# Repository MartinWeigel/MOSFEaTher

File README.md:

# MOSFEaTher

This PCB provides control of eight MOSFET outputs. These can be controlled through an [Adafruit Feather HUZZAH32](https://www.adafruit.com/product/3405) microcontroller. It is a two-layer PCB and all parts can be handsoldered in case that costs are a concern.

This board was designed using [KiCad 6.0](http://www.kicad.org).

## Design

## Parts
The board requires the following parts. All of them should be easy to handsolder:

Part                   | Quantity | Description
-----------------------|----------|----------------------------
Feather HUZZAH32       | 1        | ESP32 Microcontroller
Phoenix MPT-0,5-2-2.54 | 8        | 2-pin Terminalblock
IRLR024N DPAK MOSFET   | 8        | N-Channel MOSFET (55V 17A)
0805 Resistor 470 Ohm  | 8        | Generic Resistor

## License
<br />This work is licensed under a <a rel="license" href="http://creativecommons.org/licenses/by/4.0/">Creative Commons Attribution 4.0 International License</a>.

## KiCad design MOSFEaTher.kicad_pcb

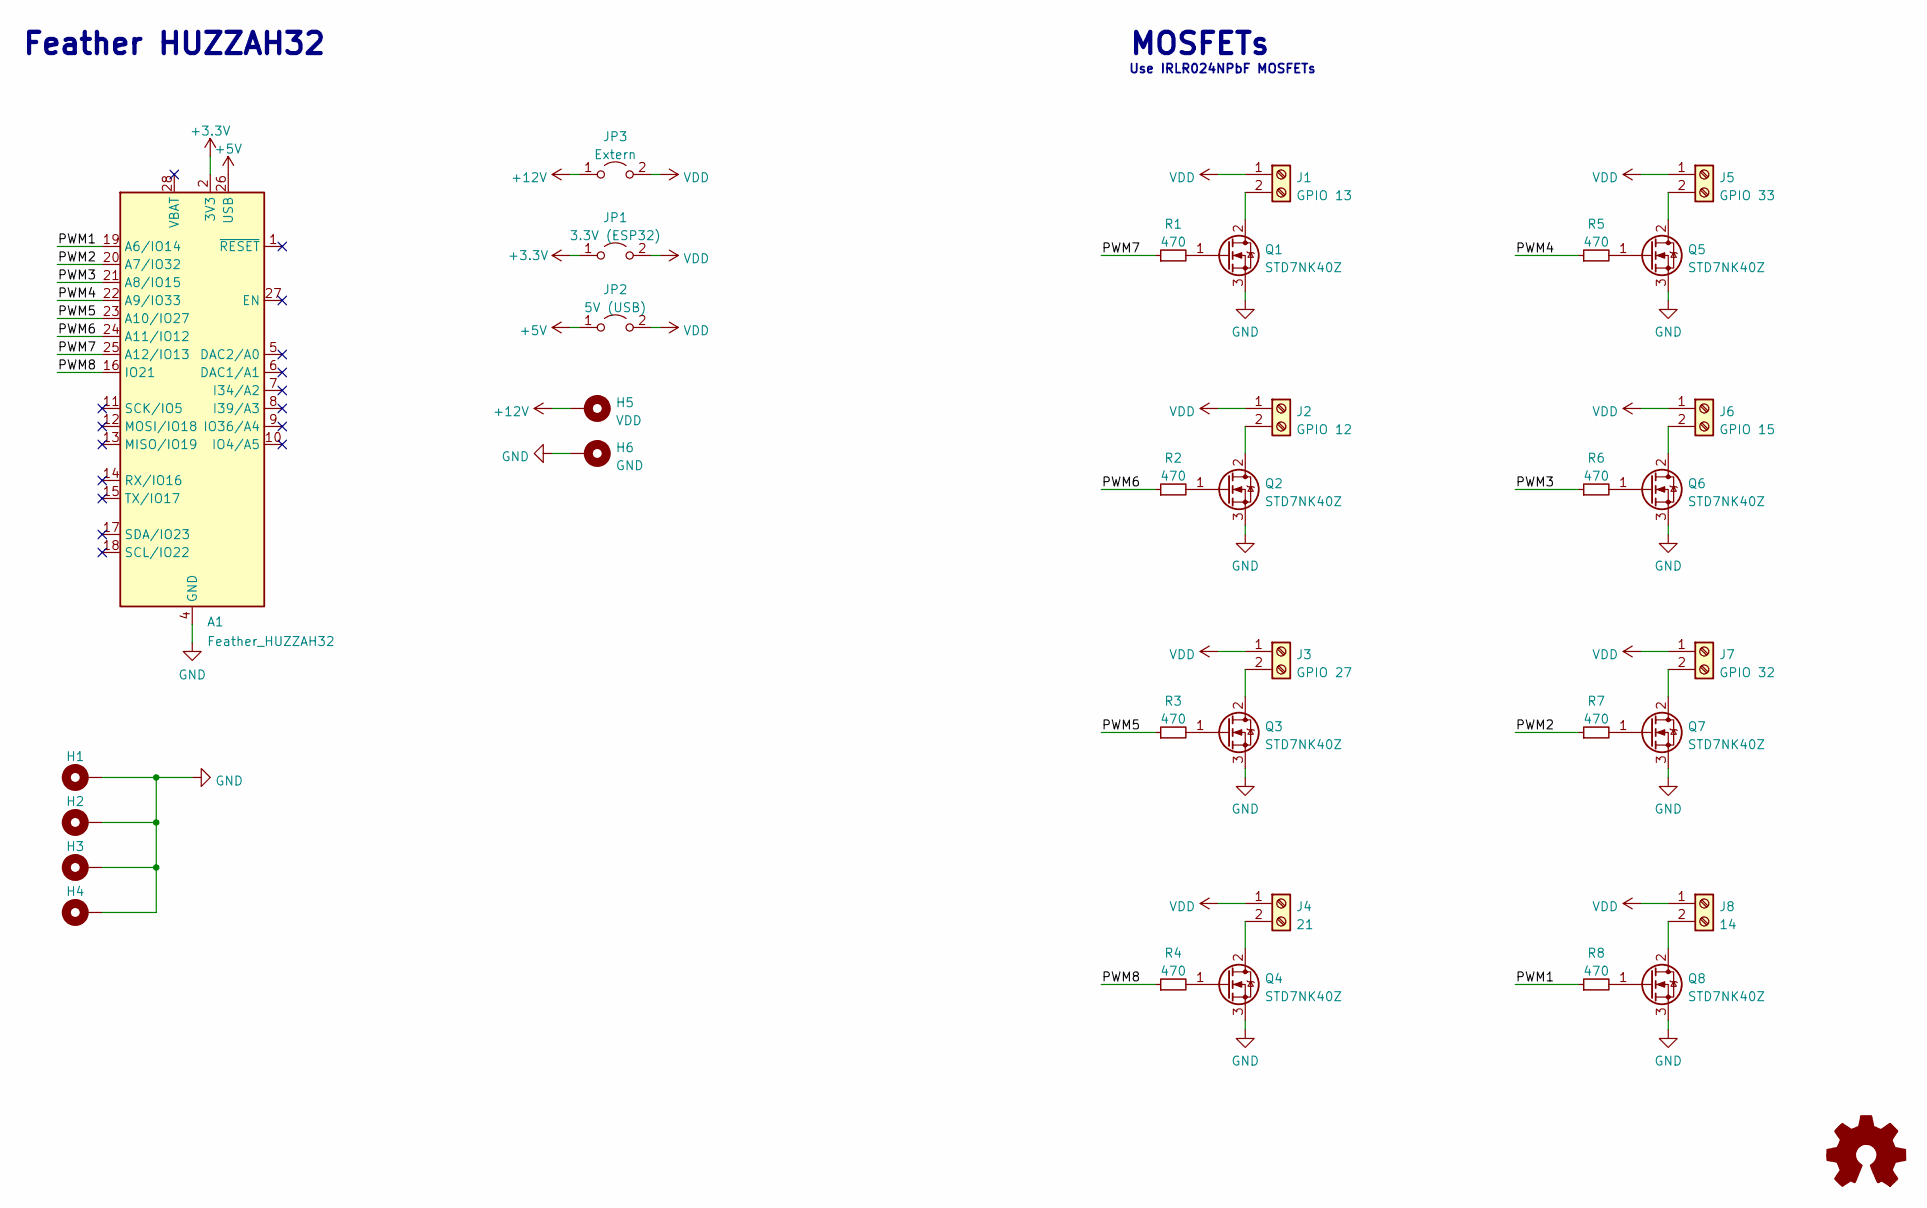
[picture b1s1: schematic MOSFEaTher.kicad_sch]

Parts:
A1: Feather_HUZZAH32; Adafruit_Feather
H1, H2, H3, H4: MountingHole_Pad; MountingHole_3.2mm_M3_DIN965_Pad
H5: VDD; TestPoint_THTPad_4.0x4.0mm_Drill2.0mm
H6: GND; TestPoint_THTPad_4.0x4.0mm_Drill2.0mm
J1: GPIO 13; TerminalBlock_Phoenix_MPT-0,5-2-2.54_1x02_P2.54mm_Horizontal
J2: GPIO 12; TerminalBlock_Phoenix_MPT-0,5-2-2.54_1x02_P2.54mm_Horizontal
J3: GPIO 27; TerminalBlock_Phoenix_MPT-0,5-2-2.54_1x02_P2.54mm_Horizontal
J4: 21; TerminalBlock_Phoenix_MPT-0,5-2-2.54_1x02_P2.54mm_Horizontal
J5: GPIO 33; TerminalBlock_Phoenix_MPT-0,5-2-2.54_1x02_P2.54mm_Horizontal
J6: GPIO 15; TerminalBlock_Phoenix_MPT-0,5-2-2.54_1x02_P2.54mm_Horizontal
J7: GPIO 32; TerminalBlock_Phoenix_MPT-0,5-2-2.54_1x02_P2.54mm_Horizontal
J8: 14; TerminalBlock_Phoenix_MPT-0,5-2-2.54_1x02_P2.54mm_Horizontal
JP1: 3.3V (ESP32); PinHeader_2x01_P2.54mm_Vertical
JP2: 5V (USB); PinHeader_2x01_P2.54mm_Vertical
JP3: Extern; PinHeader_2x01_P2.54mm_Vertical
Q1, Q2, Q3, Q4, Q5, Q6, Q7, Q8: STD7NK40Z; TO-252-2
R1, R2, R3, R4, R5, R6, R7, R8: 470; R_0805_2012Metric_Pad1.20x1.40mm_HandSolder

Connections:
+3V3: A1.2 (3V3), JP1.1 (A)
+5V: A1.26 (USB), JP2.1 (A)
+12V: H5.1, JP3.1 (A)
/PWM1: A1.19 (A6/IO14), R8.1
/PWM2: A1.20 (A7/IO32), R7.1
/PWM3: A1.21 (A8/IO15), R6.1
/PWM4: A1.22 (A9/IO33), R5.1
/PWM5: A1.23 (A10/IO27), R3.1
/PWM6: A1.24 (A11/IO12), R2.1
/PWM7: A1.25 (A12/IO13), R1.1
/PWM8: A1.16 (IO21), R4.1
GND: A1.4 (GND), H1.1, H2.1, H3.1, H4.1, H6.1, Q1.3 (S), Q2.3 (S), Q3.3 (S), Q4.3 (S), Q5.3 (S), Q6.3 (S), Q7.3 (S), Q8.3 (S)
unnamed: J1.2, Q1.2 (D)
unnamed: J2.2, Q2.2 (D)
unnamed: J3.2, Q3.2 (D)
unnamed: J4.2, Q4.2 (D)
unnamed: J5.2, Q5.2 (D)
unnamed: J6.2, Q6.2 (D)
unnamed: J7.2, Q7.2 (D)
unnamed: J8.2, Q8.2 (D)
unnamed: Q1.1 (G), R1.2
unnamed: Q2.1 (G), R2.2
unnamed: Q3.1 (G), R3.2
unnamed: Q4.1 (G), R4.2
unnamed: Q5.1 (G), R5.2
unnamed: Q6.1 (G), R6.2
unnamed: Q7.1 (G), R7.2
unnamed: Q8.1 (G), R8.2
VDD: J1.1, J2.1, J3.1, J4.1, J5.1, J6.1, J7.1, J8.1, JP1.2 (B), JP2.2 (B), JP3.2 (B)

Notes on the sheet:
Feather HUZZAH32
MOSFETs
Use IRLR024NPbF MOSFETs

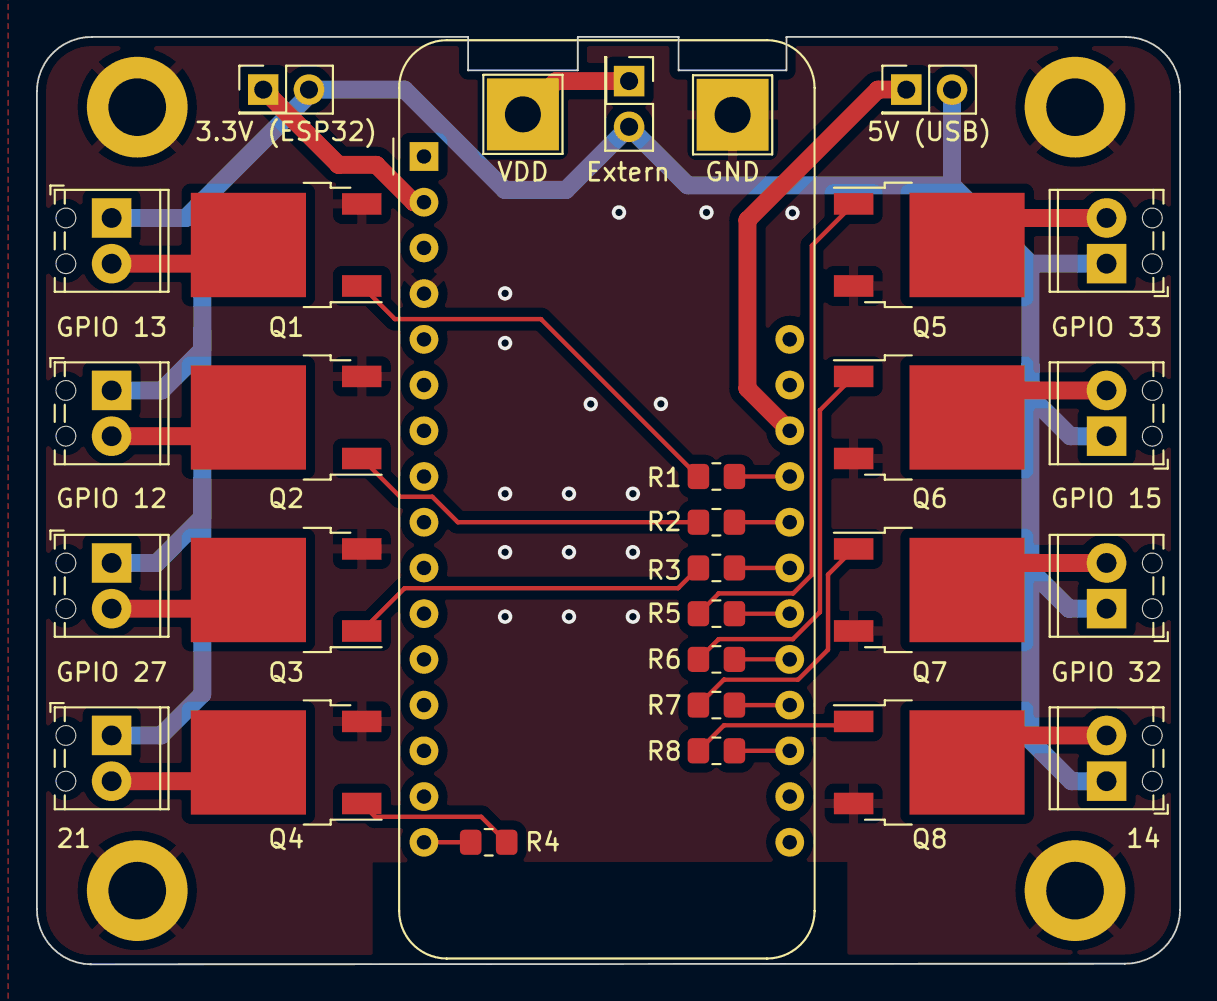
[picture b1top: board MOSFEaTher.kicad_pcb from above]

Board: 2 copper layers, 63.5 x 51.5 mm, 34 parts (0 on the bottom side), 29 nets.

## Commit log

2022-03-05 feat: first version of MOSFEaTher
2022-03-21 feat: M3 mounting holes, OSHW logo and THM affiliation
2022-05-06 feat: better power and signal routing

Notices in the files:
MOSFEaTher.kicad_pcb:
License: CC BY 4.0
